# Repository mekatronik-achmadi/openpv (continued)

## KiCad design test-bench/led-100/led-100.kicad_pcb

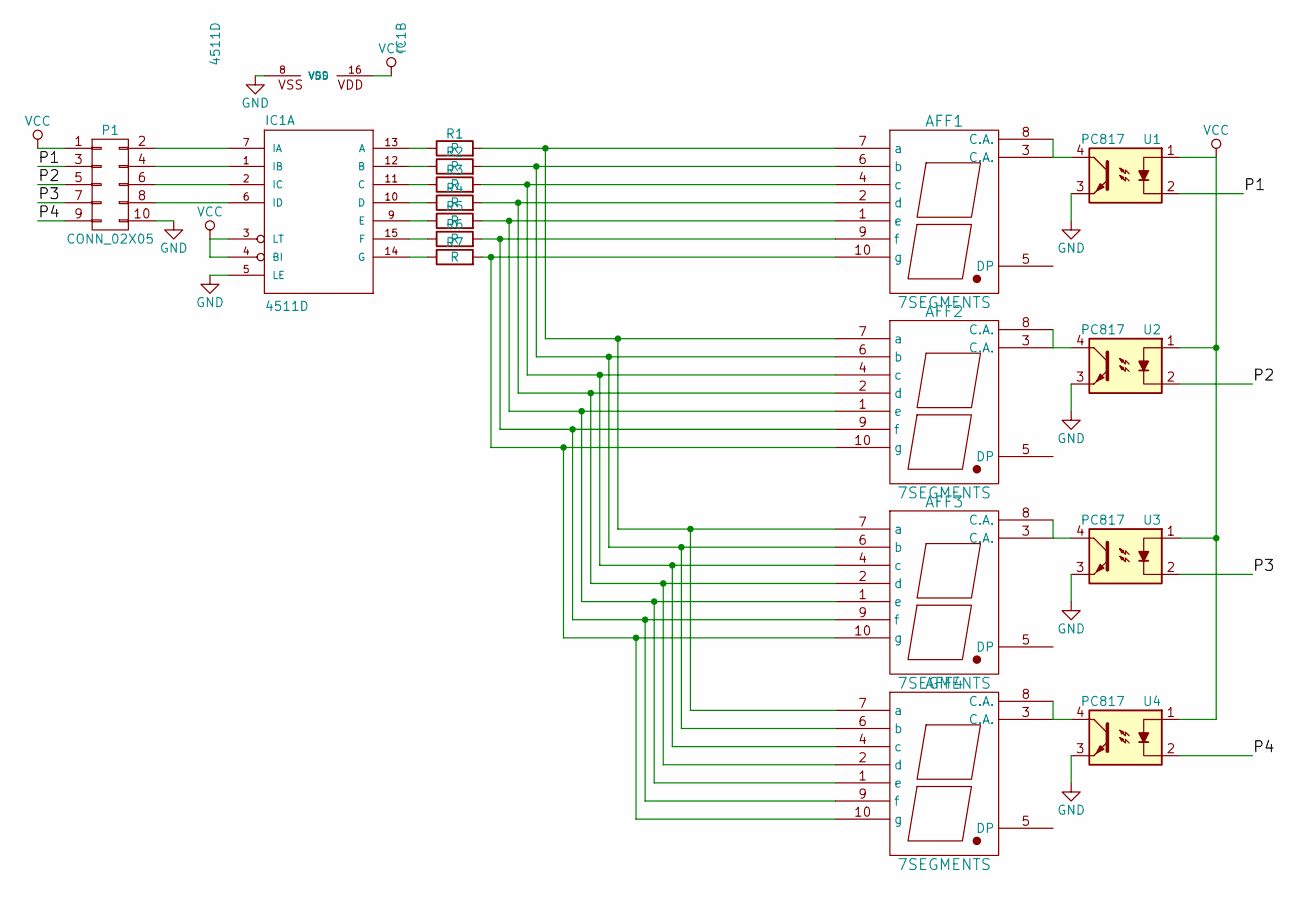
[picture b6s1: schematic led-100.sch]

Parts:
AFF1, AFF2, AFF3, AFF4: 7SEGMENTS; 7SegmentLED_LTS6760_LTS6780
IC1: 4511D; DIP-16_W7.62mm
P1: CONN_02X05; Pin_Header_Straight_2x05
R1, R2, R3, R4, R5, R6, R7: R; Resistor_Horizontal_RM10mm
U1, U2, U3, U4: PC817; DIP-4_W7.62mm

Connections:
/P1: P1.3, U1.2
/P2: P1.5, U2.2
/P3: P1.7, U3.2
/P4: P1.9, U4.2
GND: IC1.5 (LE), IC1.8 (VSS), P1.10, U1.3, U2.3, U3.3, U4.3
unnamed: AFF1.1 (e), AFF2.1 (e), AFF3.1 (e), AFF4.1 (e), R5.2
unnamed: AFF1.2 (d), AFF2.2 (d), AFF3.2 (d), AFF4.2 (d), R4.2
unnamed: AFF1.3 (C.A.), AFF1.8 (C.A.), U1.4
unnamed: AFF1.4 (c), AFF2.4 (c), AFF3.4 (c), AFF4.4 (c), R3.2
unnamed: AFF1.6 (b), AFF2.6 (b), AFF3.6 (b), AFF4.6 (b), R2.2
unnamed: AFF1.7 (a), AFF2.7 (a), AFF3.7 (a), AFF4.7 (a), R1.2
unnamed: AFF1.9 (f), AFF2.9 (f), AFF3.9 (f), AFF4.9 (f), R6.2
unnamed: AFF1.10 (g), AFF2.10 (g), AFF3.10 (g), AFF4.10 (g), R7.2
unnamed: AFF2.3 (C.A.), AFF2.8 (C.A.), U2.4
unnamed: AFF3.3 (C.A.), AFF3.8 (C.A.), U3.4
unnamed: AFF4.3 (C.A.), AFF4.8 (C.A.), U4.4
unnamed: IC1.1 (IB), P1.4
unnamed: IC1.2 (IC), P1.6
unnamed: IC1.6 (ID), P1.8
unnamed: IC1.7 (IA), P1.2
unnamed: IC1.9 (E), R5.1
unnamed: IC1.10 (D), R4.1
unnamed: IC1.11 (C), R3.1
unnamed: IC1.12 (B), R2.1
unnamed: IC1.13 (A), R1.1
unnamed: IC1.14 (G), R7.1
unnamed: IC1.15 (F), R6.1
VCC: IC1.3 (LT), IC1.4 (BI), IC1.16 (VDD), P1.1, U1.1, U2.1, U3.1, U4.1

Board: 2 copper layers, 17 parts (0 on the bottom side), 28 nets, no tracks yet.

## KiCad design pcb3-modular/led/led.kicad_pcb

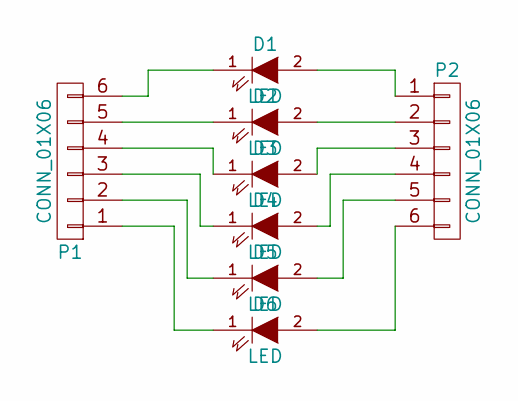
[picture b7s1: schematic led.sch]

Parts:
D1, D2, D3, D4, D5, D6: LED; LED-3MM
P1, P2: CONN_01X06; Pin_Header_Straight_1x06

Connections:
unnamed: D1.1 (K), P1.6
unnamed: D1.2 (A), P2.1
unnamed: D2.1 (K), P1.5
unnamed: D2.2 (A), P2.2
unnamed: D3.1 (K), P1.4
unnamed: D3.2 (A), P2.3
unnamed: D4.1 (K), P1.3
unnamed: D4.2 (A), P2.4
unnamed: D5.1 (K), P1.2
unnamed: D5.2 (A), P2.5
unnamed: D6.1 (K), P1.1
unnamed: D6.2 (A), P2.6

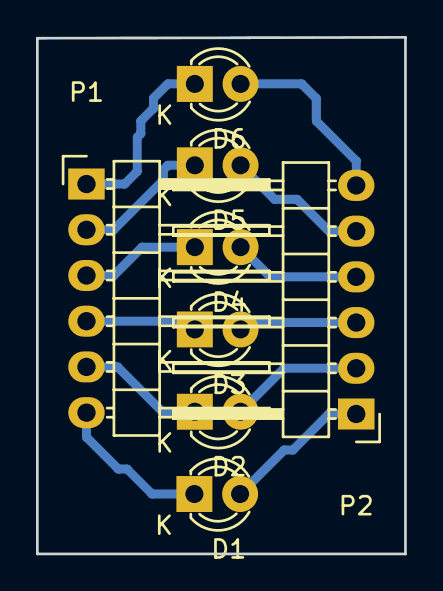
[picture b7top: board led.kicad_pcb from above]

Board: 2 copper layers, 20.5 x 28.7 mm, 8 parts (0 on the bottom side), 12 nets.

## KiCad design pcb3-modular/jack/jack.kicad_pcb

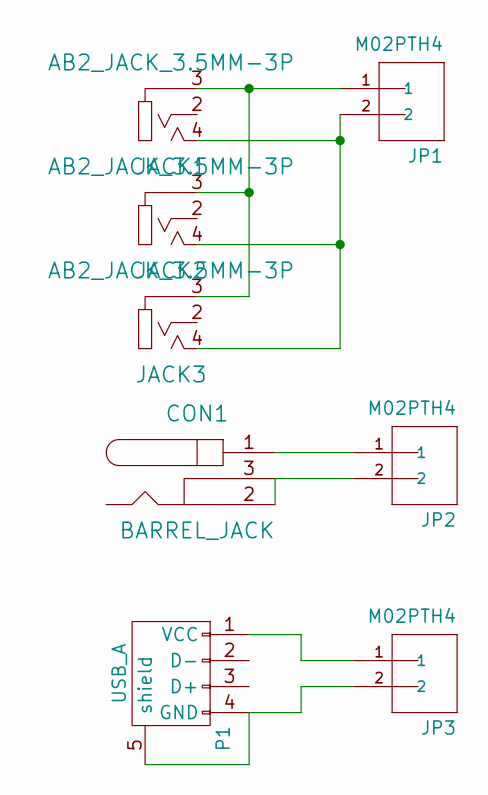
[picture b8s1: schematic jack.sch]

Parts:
CON1: BARREL_JACK; JACK_ALIM
JACK1, JACK2, JACK3: AB2_JACK_3.5MM-3P; AB2_JACK_3.5MM-3P-PTH
JP1, JP2, JP3: M02PTH4; SparkFun-1X02_XTRA_BIG
P1: USB_A

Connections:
unnamed: CON1.1, JP2.1
unnamed: CON1.2, CON1.3, JP2.2
unnamed: JACK1.3, JACK2.3, JACK3.3, JP1.1
unnamed: JACK1.4, JACK2.4, JACK3.4, JP1.2
unnamed: JP3.1, P1.1 (VCC)
unnamed: JP3.2, P1.4 (GND), P1.5 (shield)

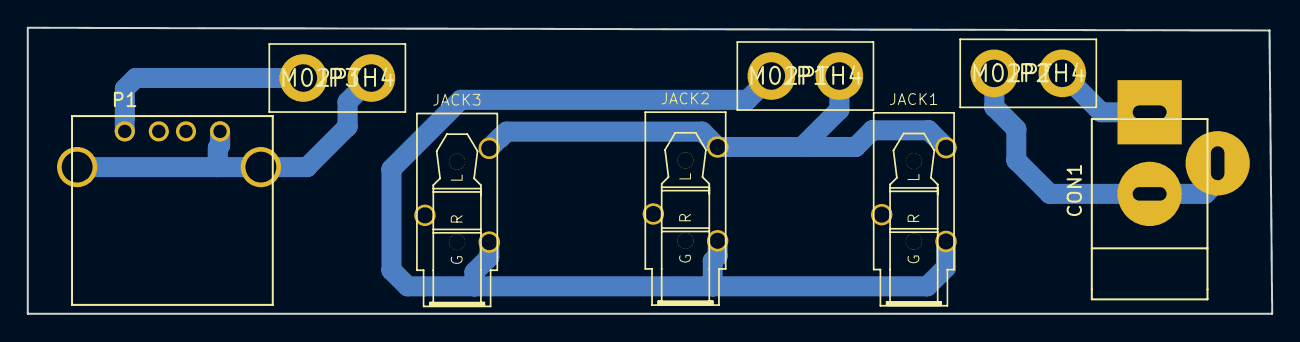
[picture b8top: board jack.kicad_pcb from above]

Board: 2 copper layers, 92.9 x 21.3 mm, 8 parts (0 on the bottom side), 6 nets.

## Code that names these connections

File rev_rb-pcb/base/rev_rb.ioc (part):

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Mcu.Name=STM32F103R(8-B)Tx
Mcu.Package=LQFP64
PA0-WKUP.Mode=IN0
PA0-WKUP.Signal=ADC1_IN0
PA1.Mode=IN1
PA1.Signal=ADC1_IN1
PA10.Mode=Asynchronous
PA10.Signal=USART1_RX
PA2.Mode=IN2
PA2.Signal=ADC1_IN2
PA3.Mode=IN3
PA3.Signal=ADC1_IN3
PA4.Mode=IN4
PA4.Signal=ADC1_IN4
PA5.Mode=IN5
PA5.Signal=ADC1_IN5
PA6.Mode=IN6
PA6.Signal=ADC1_IN6
PA7.Mode=IN7
PA7.Signal=ADC1_IN7
PA9.Mode=Asynchronous
PA9.Signal=USART1_TX
PB12.Signal=GPIO_Output
PB13.Signal=GPIO_Output
PB14.Signal=GPIO_Output
PB15.Signal=GPIO_Input
PB2.Mode=Event-Out
PB2.Signal=CORTEX_EVENT_OUT
PB3.Signal=GPIO_Output
PB4.Signal=GPIO_Output
PB5.Signal=GPIO_Output
PB6.Signal=GPIO_Output
PB7.Signal=GPIO_Output
PB8.Signal=GPIO_Output
PB9.Signal=GPIO_Output
PC14-OSC32_IN.Mode=LSE-External-Oscillator
PC14-OSC32_IN.Signal=SYS_OSC32_IN
PC15-OSC32_OUT.Mode=LSE-External-Oscillator
PC15-OSC32_OUT.Signal=SYS_OSC32_OUT
PD0-OSC_IN.Mode=HSE-External-Oscillator
PD0-OSC_IN.Signal=SYS_OSC_IN
PD1-OSC_OUT.Mode=HSE-External-Oscillator
PD1-OSC_OUT.Signal=SYS_OSC_OUT

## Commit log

2015-05-29 Pengujian tahap 1
2015-08-05 seri 2.0
2015-08-05 ready to facturing
2015-08-06 add mount holes
2015-08-22 second devs
2015-09-02 ADC test
2015-09-02 Ready for more Test
2015-09-02 After Pull
2015-09-18 interface ready to test
2015-10-08 current monitoring
2015-10-12 ready to test
2015-10-23 drain-charge test based on voltage
2015-10-24 user serial
2015-10-24 catatan perbaikan
2015-10-27 new PCB (KiCAD standard)
2015-11-01 belum apply revisi
2015-11-02 ready to build
2015-11-05 fabricate
2015-11-19 capek coyy
2015-11-25 capeeek
2015-12-04 rilis design
2015-12-04 next:assembly manual
2015-12-04 manual book
2015-12-05 send to fabrication
2015-12-06 diplay
2015-12-14 Display Main Controller
2015-12-14 display nilai
2015-12-15 design display beres
2015-12-15 lapooor
2016-01-14 big work
2016-01-21 LED lamp use SMD 1206 Resistor
2016-01-22 revisi
2016-01-28 7 Segment On
2016-02-09 display use RTOS
2016-02-09 single data OK
2016-02-09 test sim
2016-02-12 display tinggal jam-tanggal
2016-02-17 next gen PSHS
2016-02-22 4-digit for source intensity
2016-02-22 base schematic
2016-02-23 learn sleep mode
2016-02-25 begins
2016-02-29 progress
2016-03-07 test diagram
2016-03-07 new print
2016-03-09 try again
2016-03-16 standby mode
2016-04-09 chibios cannot use stm32lib's Interrupt Handler
2016-04-09 STDLib build using Chibios's Makefile
2016-04-09 stop-run by RTC
2016-04-10 use system-wide build Makefile
2016-04-11 split API
2016-04-11 test
2016-04-16 development
2016-04-16 sial
2016-04-18 rtc ok
2016-04-18 RTC Sleep working
2016-04-18 sleep test
2016-04-19 next: baterai level
2016-04-19 all pin ok
